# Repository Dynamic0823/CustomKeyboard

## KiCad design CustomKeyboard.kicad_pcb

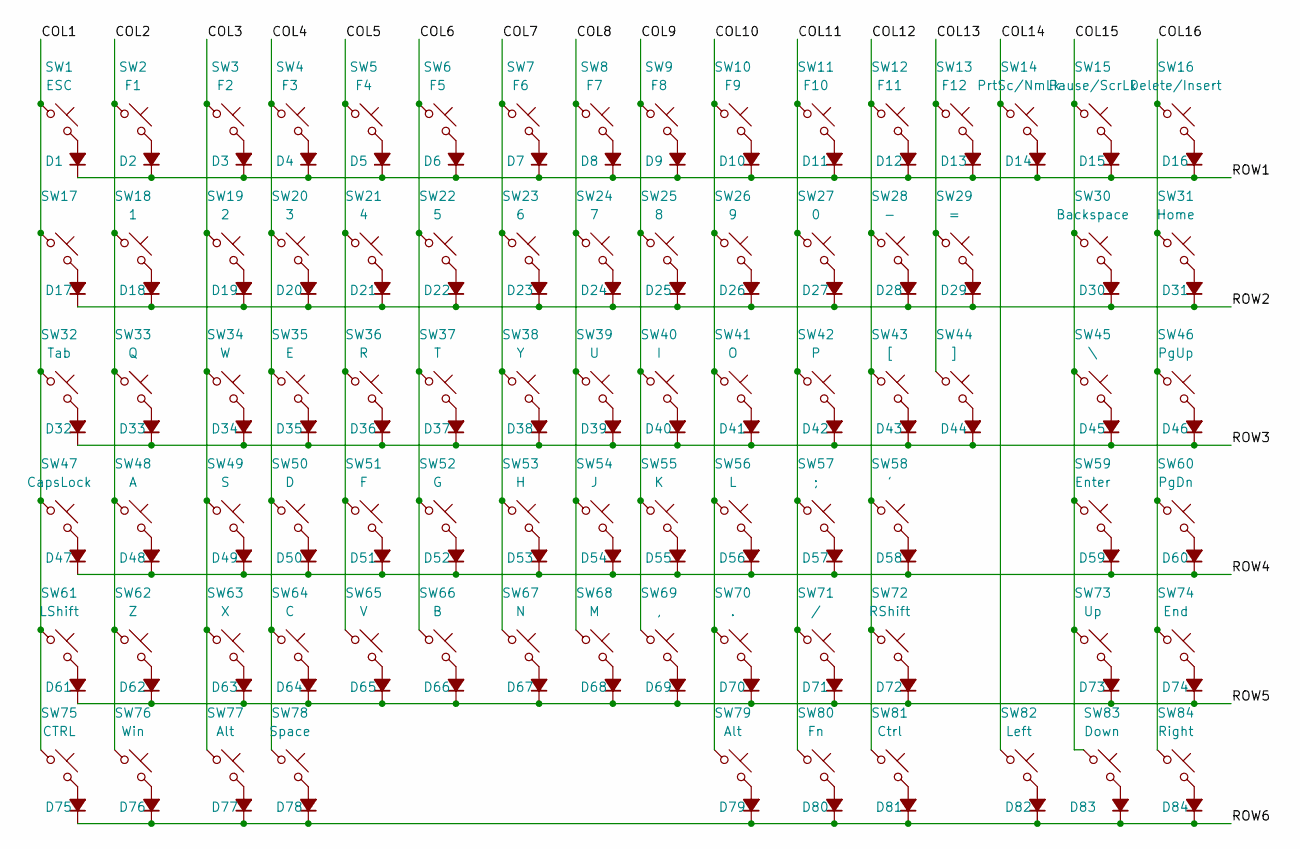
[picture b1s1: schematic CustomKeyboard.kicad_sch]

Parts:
D1, D2, D3, D4, D5, D6, D7, D8, D9, D10, D11, D12, D13, D14, D15, D16, D17, D18, D19, D20, D21, D22, D23, D24, D25, D26, D27, D28, D29, D30, D31, D32, D33, D34, D35, D36, D37, D38, D39, D40, D41, D42, D43, D44, D45, D46, D47, D48, D49, D50, D51, D52, D53, D54, D55, D56, D57, D58, D59, D60, D61, D62, D63, D64, D65, D66, D67, D68, D69, D70, D71, D72, D73, D74, D75, D76, D77, D78, D79, D80, D81, D82, D83, D84: D_Small_Filled; D_0805_2012Metric_Pad1.15x1.40mm_HandSolder
SW1: ESC; SW_Hotswap_Kailh_Choc_V1V2_Plated_1.00u
SW2: F1; SW_Hotswap_Kailh_Choc_V1V2_Plated_1.00u
SW3: F2; SW_Hotswap_Kailh_Choc_V1V2_Plated_1.00u
SW4: F3; SW_Hotswap_Kailh_Choc_V1V2_Plated_1.00u
SW5: F4; SW_Hotswap_Kailh_Choc_V1V2_Plated_1.00u
SW6: F5; SW_Hotswap_Kailh_Choc_V1V2_Plated_1.00u
SW7: F6; SW_Hotswap_Kailh_Choc_V1V2_Plated_1.00u
SW8: F7; SW_Hotswap_Kailh_Choc_V1V2_Plated_1.00u
SW9: F8; SW_Hotswap_Kailh_Choc_V1V2_Plated_1.00u
SW10: F9; SW_Hotswap_Kailh_Choc_V1V2_Plated_1.00u
SW11: F10; SW_Hotswap_Kailh_Choc_V1V2_Plated_1.00u
SW12: F11; SW_Hotswap_Kailh_Choc_V1V2_Plated_1.00u
SW13: F12; SW_Hotswap_Kailh_Choc_V1V2_Plated_1.00u
SW14: PrtSc/NmLk; SW_Hotswap_Kailh_Choc_V1V2_Plated_1.00u
SW15: Pause/ScrLk; SW_Hotswap_Kailh_Choc_V1V2_Plated_1.00u
SW16: Delete/Insert; SW_Hotswap_Kailh_Choc_V1V2_Plated_1.00u
SW17: SW_Hotswap_Kailh_Choc_V1V2_Plated_1.00u
SW18: 1; SW_Hotswap_Kailh_Choc_V1V2_Plated_1.00u
SW19: 2; SW_Hotswap_Kailh_Choc_V1V2_Plated_1.00u
SW20: 3; SW_Hotswap_Kailh_Choc_V1V2_Plated_1.00u
SW21: 4; SW_Hotswap_Kailh_Choc_V1V2_Plated_1.00u
SW22: 5; SW_Hotswap_Kailh_Choc_V1V2_Plated_1.00u
SW23: 6; SW_Hotswap_Kailh_Choc_V1V2_Plated_1.00u
SW24: 7; SW_Hotswap_Kailh_Choc_V1V2_Plated_1.00u
SW25: 8; SW_Hotswap_Kailh_Choc_V1V2_Plated_1.00u
SW26: 9; SW_Hotswap_Kailh_Choc_V1V2_Plated_1.00u
SW27: 0; SW_Hotswap_Kailh_Choc_V1V2_Plated_1.00u
SW28: -; SW_Hotswap_Kailh_Choc_V1V2_Plated_1.00u
SW29: =; SW_Hotswap_Kailh_Choc_V1V2_Plated_1.00u
SW30: Backspace; SW_Hotswap_Kailh_Choc_V1V2_Plated_2.00u
SW31: Home; SW_Hotswap_Kailh_Choc_V1V2_Plated_1.00u
SW32: Tab; SW_Hotswap_Kailh_Choc_V1V2_Plated_1.50u
SW33: Q; SW_Hotswap_Kailh_Choc_V1V2_Plated_1.00u
SW34: W; SW_Hotswap_Kailh_Choc_V1V2_Plated_1.00u
SW35: E; SW_Hotswap_Kailh_Choc_V1V2_Plated_1.00u
SW36: R; SW_Hotswap_Kailh_Choc_V1V2_Plated_1.00u
SW37: T; SW_Hotswap_Kailh_Choc_V1V2_Plated_1.00u
SW38: Y; SW_Hotswap_Kailh_Choc_V1V2_Plated_1.00u
SW39: U; SW_Hotswap_Kailh_Choc_V1V2_Plated_1.00u
SW40: I; SW_Hotswap_Kailh_Choc_V1V2_Plated_1.00u
SW41: O; SW_Hotswap_Kailh_Choc_V1V2_Plated_1.00u
SW42: P; SW_Hotswap_Kailh_Choc_V1V2_Plated_1.00u
SW43: [; SW_Hotswap_Kailh_Choc_V1V2_Plated_1.00u
SW44: ]; SW_Hotswap_Kailh_Choc_V1V2_Plated_1.00u
SW45: \; SW_Hotswap_Kailh_Choc_V1V2_Plated_1.50u
SW46: PgUp; SW_Hotswap_Kailh_Choc_V1V2_Plated_1.00u
SW47: CapsLock; SW_Hotswap_Kailh_Choc_V1V2_Plated_1.75u
SW48: A; SW_Hotswap_Kailh_Choc_V1V2_Plated_1.00u
SW49: S; SW_Hotswap_Kailh_Choc_V1V2_Plated_1.00u
SW50: D; SW_Hotswap_Kailh_Choc_V1V2_Plated_1.00u
SW51: F; SW_Hotswap_Kailh_Choc_V1V2_Plated_1.00u
SW52: G; SW_Hotswap_Kailh_Choc_V1V2_Plated_1.00u
SW53: H; SW_Hotswap_Kailh_Choc_V1V2_Plated_1.00u
SW54: J; SW_Hotswap_Kailh_Choc_V1V2_Plated_1.00u
SW55: K; SW_Hotswap_Kailh_Choc_V1V2_Plated_1.00u
SW56: L; SW_Hotswap_Kailh_Choc_V1V2_Plated_1.00u
SW57: ;; SW_Hotswap_Kailh_Choc_V1V2_Plated_1.00u
SW58: '; SW_Hotswap_Kailh_Choc_V1V2_Plated_1.00u
SW59: Enter; SW_Hotswap_Kailh_Choc_V1V2_Plated_2.25u
SW60: PgDn; SW_Hotswap_Kailh_Choc_V1V2_Plated_1.00u
SW61: LShift; SW_Hotswap_Kailh_Choc_V1V2_Plated_2.25u
SW62: Z; SW_Hotswap_Kailh_Choc_V1V2_Plated_1.00u
SW63: X; SW_Hotswap_Kailh_Choc_V1V2_Plated_1.00u
SW64: C; SW_Hotswap_Kailh_Choc_V1V2_Plated_1.00u
SW65: V; SW_Hotswap_Kailh_Choc_V1V2_Plated_1.00u
SW66: B; SW_Hotswap_Kailh_Choc_V1V2_Plated_1.00u
SW67: N; SW_Hotswap_Kailh_Choc_V1V2_Plated_1.00u
SW68: M; SW_Hotswap_Kailh_Choc_V1V2_Plated_1.00u
SW69: ,; SW_Hotswap_Kailh_Choc_V1V2_Plated_1.00u
SW70: .; SW_Hotswap_Kailh_Choc_V1V2_Plated_1.00u
SW71: /; SW_Hotswap_Kailh_Choc_V1V2_Plated_1.00u
SW72: RShift; SW_Hotswap_Kailh_Choc_V1V2_Plated_1.75u
SW73: Up; SW_Hotswap_Kailh_Choc_V1V2_Plated_1.00u
SW74: End; SW_Hotswap_Kailh_Choc_V1V2_Plated_1.00u
SW75: CTRL; SW_Hotswap_Kailh_Choc_V1V2_Plated_1.25u
SW76: Win; SW_Hotswap_Kailh_Choc_V1V2_Plated_1.25u
SW77: Alt; SW_Hotswap_Kailh_Choc_V1V2_Plated_1.25u
SW78: Space; SW_Hotswap_Kailh_Choc_V1V2_Plated_6.25u
SW79: Alt; SW_Hotswap_Kailh_Choc_V1V2_Plated_1.00u
SW80: Fn; SW_Hotswap_Kailh_Choc_V1V2_Plated_1.00u
SW81: Ctrl; SW_Hotswap_Kailh_Choc_V1V2_Plated_1.00u
SW82: Left; SW_Hotswap_Kailh_Choc_V1V2_Plated_1.00u
SW83: Down; SW_Hotswap_Kailh_Choc_V1V2_Plated_1.00u
SW84: Right; SW_Hotswap_Kailh_Choc_V1V2_Plated_1.00u

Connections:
/COL1: SW1.1, SW17.1, SW32.1, SW47.1, SW61.1, SW75.1; also elsewhere on the board
/COL2: SW2.1, SW18.1, SW33.1, SW48.1, SW62.1, SW76.1; also elsewhere on the board
/COL3: SW3.1, SW19.1, SW34.1, SW49.1, SW63.1, SW77.1; also elsewhere on the board
/COL4: SW4.1, SW20.1, SW35.1, SW50.1, SW64.1, SW78.1; also elsewhere on the board
/COL5: SW5.1, SW21.1, SW36.1, SW51.1, SW65.1; also elsewhere on the board
/COL6: SW6.1, SW22.1, SW37.1, SW52.1, SW66.1; also elsewhere on the board
/COL7: SW7.1, SW23.1, SW38.1, SW53.1, SW67.1; also elsewhere on the board
/COL8: SW8.1, SW24.1, SW39.1, SW54.1, SW68.1; also elsewhere on the board
/COL9: SW9.1, SW25.1, SW40.1, SW55.1, SW69.1; also elsewhere on the board
/COL10: SW10.1, SW26.1, SW41.1, SW56.1, SW70.1, SW79.1; also elsewhere on the board
/COL11: SW11.1, SW27.1, SW42.1, SW57.1, SW71.1, SW80.1; also elsewhere on the board
/COL12: SW12.1, SW28.1, SW43.1, SW58.1, SW72.1, SW81.1; also elsewhere on the board
/COL13: SW13.1, SW29.1, SW44.1; also elsewhere on the board
/COL14: SW14.1, SW82.1; also elsewhere on the board
/COL15: SW15.1, SW30.1, SW45.1, SW59.1, SW73.1, SW83.1; also elsewhere on the board
/COL16: SW16.1, SW31.1, SW46.1, SW60.1, SW74.1, SW84.1; also elsewhere on the board
/ROW1: D1.1 (K), D2.1 (K), D3.1 (K), D4.1 (K), D5.1 (K), D6.1 (K), D7.1 (K), D8.1 (K), D9.1 (K), D10.1 (K), D11.1 (K), D12.1 (K), D13.1 (K), D14.1 (K), D15.1 (K), D16.1 (K); also elsewhere on the board
/ROW2: D17.1 (K), D18.1 (K), D19.1 (K), D20.1 (K), D21.1 (K), D22.1 (K), D23.1 (K), D24.1 (K), D25.1 (K), D26.1 (K), D27.1 (K), D28.1 (K), D29.1 (K), D30.1 (K), D31.1 (K); also elsewhere on the board
/ROW3: D32.1 (K), D33.1 (K), D34.1 (K), D35.1 (K), D36.1 (K), D37.1 (K), D38.1 (K), D39.1 (K), D40.1 (K), D41.1 (K), D42.1 (K), D43.1 (K), D44.1 (K), D45.1 (K), D46.1 (K); also elsewhere on the board
/ROW4: D47.1 (K), D48.1 (K), D49.1 (K), D50.1 (K), D51.1 (K), D52.1 (K), D53.1 (K), D54.1 (K), D55.1 (K), D56.1 (K), D57.1 (K), D58.1 (K), D59.1 (K), D60.1 (K); also elsewhere on the board
/ROW5: D61.1 (K), D62.1 (K), D63.1 (K), D64.1 (K), D65.1 (K), D66.1 (K), D67.1 (K), D68.1 (K), D69.1 (K), D70.1 (K), D71.1 (K), D72.1 (K), D73.1 (K), D74.1 (K); also elsewhere on the board
/ROW6: D75.1 (K), D76.1 (K), D77.1 (K), D78.1 (K), D79.1 (K), D80.1 (K), D81.1 (K), D82.1 (K), D83.1 (K), D84.1 (K); also elsewhere on the board
unnamed: D1.2 (A), SW1.2
unnamed: D2.2 (A), SW2.2
unnamed: D3.2 (A), SW3.2
unnamed: D4.2 (A), SW4.2
unnamed: D5.2 (A), SW5.2
unnamed: D6.2 (A), SW6.2
unnamed: D7.2 (A), SW7.2
unnamed: D8.2 (A), SW8.2
unnamed: D9.2 (A), SW9.2
unnamed: D10.2 (A), SW10.2
unnamed: D11.2 (A), SW11.2
unnamed: D12.2 (A), SW12.2
unnamed: D13.2 (A), SW13.2
unnamed: D14.2 (A), SW14.2
unnamed: D15.2 (A), SW15.2
unnamed: D16.2 (A), SW16.2
unnamed: D17.2 (A), SW17.2
unnamed: D18.2 (A), SW18.2
unnamed: D19.2 (A), SW19.2
unnamed: D20.2 (A), SW20.2
unnamed: D21.2 (A), SW21.2
unnamed: D22.2 (A), SW22.2
unnamed: D23.2 (A), SW23.2
unnamed: D24.2 (A), SW24.2
unnamed: D25.2 (A), SW25.2
unnamed: D26.2 (A), SW26.2
unnamed: D27.2 (A), SW27.2
unnamed: D28.2 (A), SW28.2
unnamed: D29.2 (A), SW29.2
unnamed: D30.2 (A), SW30.2
unnamed: D31.2 (A), SW31.2
unnamed: D32.2 (A), SW32.2
unnamed: D33.2 (A), SW33.2
unnamed: D34.2 (A), SW34.2
unnamed: D35.2 (A), SW35.2
unnamed: D36.2 (A), SW36.2
unnamed: D37.2 (A), SW37.2
unnamed: D38.2 (A), SW38.2
unnamed: D39.2 (A), SW39.2
unnamed: D40.2 (A), SW40.2
unnamed: D41.2 (A), SW41.2
unnamed: D42.2 (A), SW42.2
unnamed: D43.2 (A), SW43.2
unnamed: D44.2 (A), SW44.2
unnamed: D45.2 (A), SW45.2
unnamed: D46.2 (A), SW46.2
unnamed: D47.2 (A), SW47.2
unnamed: D48.2 (A), SW48.2
unnamed: D49.2 (A), SW49.2
unnamed: D50.2 (A), SW50.2
unnamed: D51.2 (A), SW51.2
unnamed: D52.2 (A), SW52.2
unnamed: D53.2 (A), SW53.2
unnamed: D54.2 (A), SW54.2
unnamed: D55.2 (A), SW55.2
unnamed: D56.2 (A), SW56.2
unnamed: D57.2 (A), SW57.2
unnamed: D58.2 (A), SW58.2
unnamed: D59.2 (A), SW59.2
unnamed: D60.2 (A), SW60.2
unnamed: D61.2 (A), SW61.2
unnamed: D62.2 (A), SW62.2
unnamed: D63.2 (A), SW63.2
unnamed: D64.2 (A), SW64.2
unnamed: D65.2 (A), SW65.2
unnamed: D66.2 (A), SW66.2
unnamed: D67.2 (A), SW67.2
unnamed: D68.2 (A), SW68.2
unnamed: D69.2 (A), SW69.2
unnamed: D70.2 (A), SW70.2
unnamed: D71.2 (A), SW71.2
unnamed: D72.2 (A), SW72.2
unnamed: D73.2 (A), SW73.2
unnamed: D74.2 (A), SW74.2
unnamed: D75.2 (A), SW75.2
unnamed: D76.2 (A), SW76.2
unnamed: D77.2 (A), SW77.2
unnamed: D78.2 (A), SW78.2
unnamed: D79.2 (A), SW79.2
unnamed: D80.2 (A), SW80.2
unnamed: D81.2 (A), SW81.2
unnamed: D82.2 (A), SW82.2
unnamed: D83.2 (A), SW83.2
unnamed: D84.2 (A), SW84.2

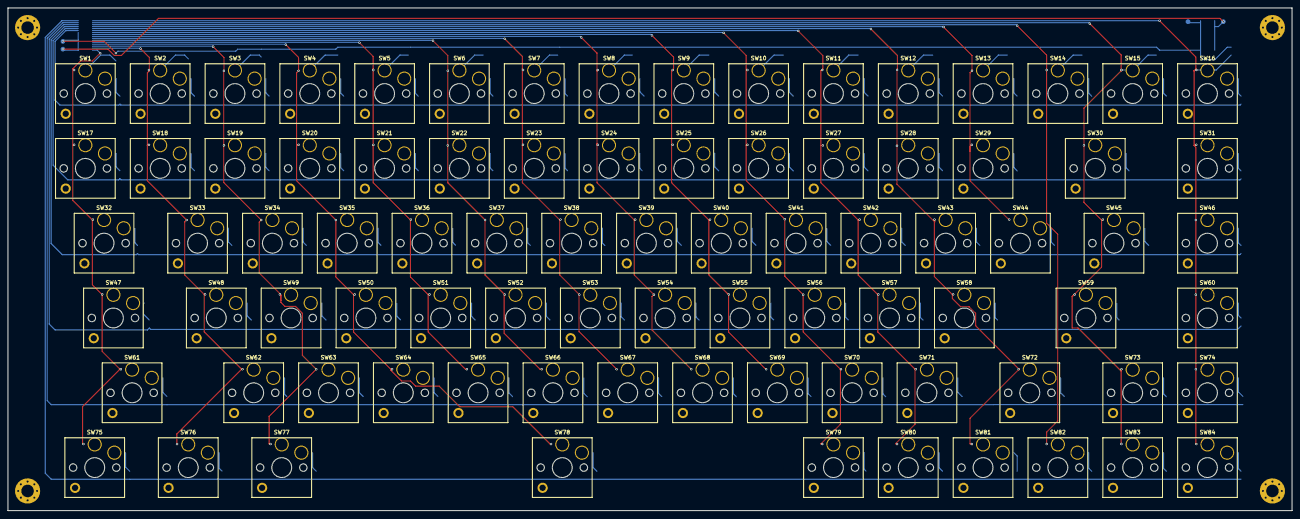
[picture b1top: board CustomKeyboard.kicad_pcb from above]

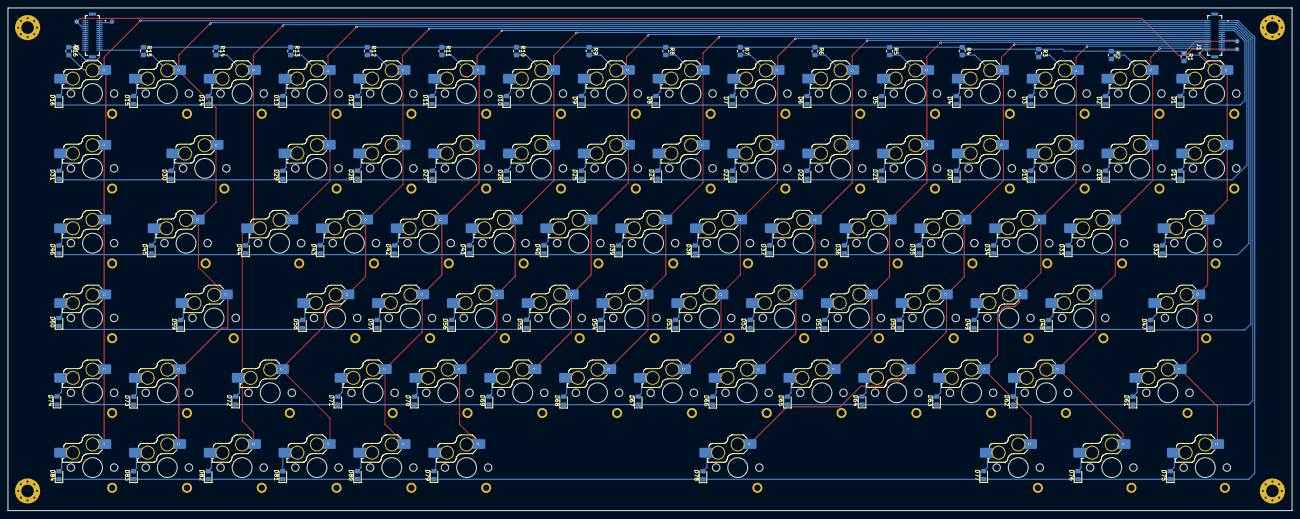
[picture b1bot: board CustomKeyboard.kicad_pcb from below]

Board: 2 copper layers, 327.0 x 128.0 mm, 190 parts (102 on the bottom side), 108 nets.

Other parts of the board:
H1, H2, H3, H4: MountingHole; MountingHole_3.2mm_M3_Pad_Via
J1, J2: Conn_02x16_Odd_Even; HRS_DF12NB_3.0_-32DS-0.5V_51_
R1, R2, R3, R4, R5, R6, R7, R8, R9, R10, R11, R12, R13, R14, R15, R16: 10k; R_0805_2012Metric_Pad1.20x1.40mm_HandSolder

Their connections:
+3.3V: J1.13, J1.15, J1.17, J1.19, J1.21, J2.1, J2.3, J2.5, J2.7, J2.9, J2.11, J2.13, J2.15, J2.17, J2.19, J2.21, J2.23, J2.25, J2.27, J2.29, J2.31, R1.1, R2.1, R3.1, R4.1, R5.1, R6.1, R7.1, R8.1, R9.1, R10.1, R11.1, R12.1, R13.1, R14.1, R15.1, R16.1
/COL1: J1.32, R1.2; also elsewhere on the board
/COL2: J1.30, R2.2; also elsewhere on the board
/COL3: J1.28, R3.2; also elsewhere on the board
/COL4: J1.26, R4.2; also elsewhere on the board
/COL5: J1.24, R5.2; also elsewhere on the board
/COL6: J1.22, R6.2; also elsewhere on the board
/COL7: J1.20, R7.2; also elsewhere on the board
/COL8: J1.18, R8.2; also elsewhere on the board
/COL9: J1.16, R9.2; also elsewhere on the board
/COL10: J1.14, R10.2; also elsewhere on the board
/COL11: J1.12, R11.2; also elsewhere on the board
/COL12: J1.10, R12.2; also elsewhere on the board
/COL13: J1.8, R13.2; also elsewhere on the board
/COL14: J1.6, R14.2; also elsewhere on the board
/COL15: J1.4, R15.2; also elsewhere on the board
/COL16: J1.2, R16.2; also elsewhere on the board
/ROW1: J1.11; also elsewhere on the board
/ROW2: J1.9; also elsewhere on the board
/ROW3: J1.7; also elsewhere on the board
/ROW4: J1.5; also elsewhere on the board
/ROW5: J1.3; also elsewhere on the board
/ROW6: J1.1; also elsewhere on the board
GND: J1.23, J1.25, J1.27, J1.29, J1.31, J2.2, J2.4, J2.6, J2.8, J2.10, J2.12, J2.14, J2.16, J2.18, J2.20, J2.22, J2.24, J2.26, J2.28, J2.30, J2.32

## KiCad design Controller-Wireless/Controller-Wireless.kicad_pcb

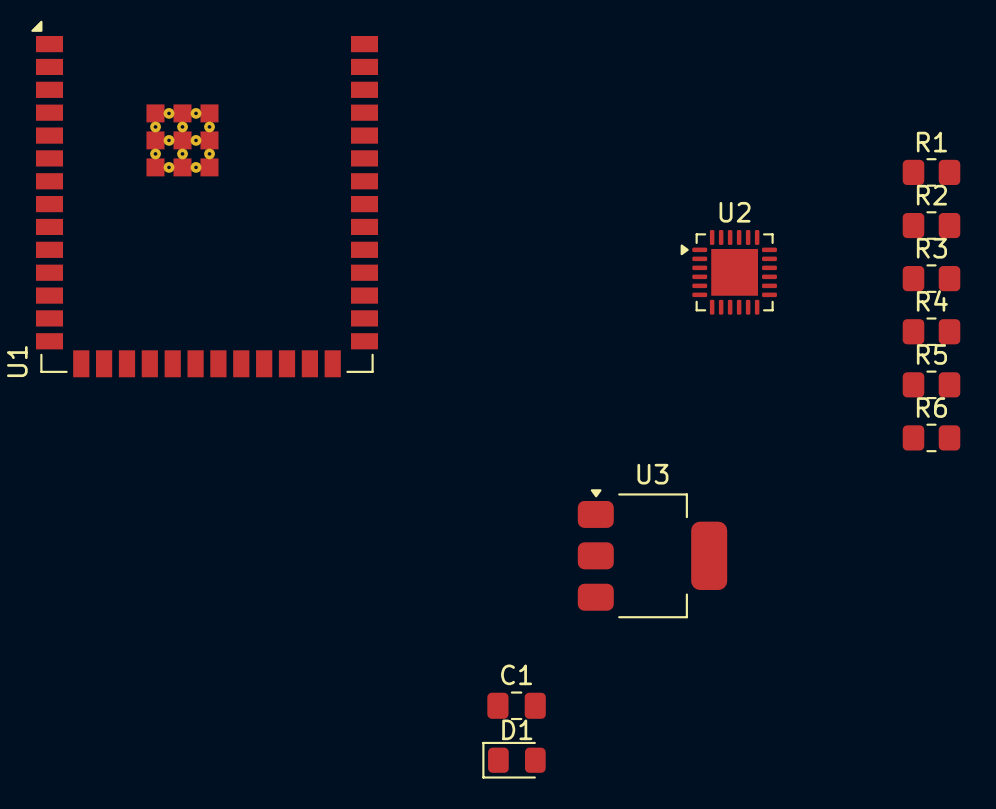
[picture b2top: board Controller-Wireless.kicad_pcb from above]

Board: 2 copper layers, 11 parts (0 on the bottom side), 9 nets, no tracks yet.

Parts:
C1: C_Small; C_0805_2012Metric_Pad1.18x1.45mm_HandSolder
D1: LED; D_0805_2012Metric_Pad1.15x1.40mm_HandSolder
R1, R2, R3, R6: 470; R_0805_2012Metric_Pad1.20x1.40mm_HandSolder
R4: 12K; R_0805_2012Metric_Pad1.20x1.40mm_HandSolder
R5: 12k; R_0805_2012Metric_Pad1.20x1.40mm_HandSolder
U1: ESP32-S3-WROOM-2
U2: CP2102N-Axx-xQFN24; QFN-24-1EP_4x4mm_P0.5mm_EP2.6x2.6mm
U3: AMS1117-3.3; SOT-223-3_TabPin2

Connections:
/EN: R2.2, R4.1, U1.3 (EN)
/IO0: R3.2, R5.1, U1.27 (IO0)
/U0Rx: R6.2, U1.36 (RXD0/IO44)
/U0Tx: U1.37 (TXD0/IO43), U2.21 (TXD)
GND: D1.1 (K), U1.1 (GND), U1.40 (GND), U1.41 (GND), U2.2 (GND), U2.25 (GND)
unnamed: D1.2 (A), R1.2
unnamed: R1.1, U1.38 (IO2)
unnamed: R6.1, U2.20 (RXD)
VDD: R4.2, R5.2, U1.2 (3V3)

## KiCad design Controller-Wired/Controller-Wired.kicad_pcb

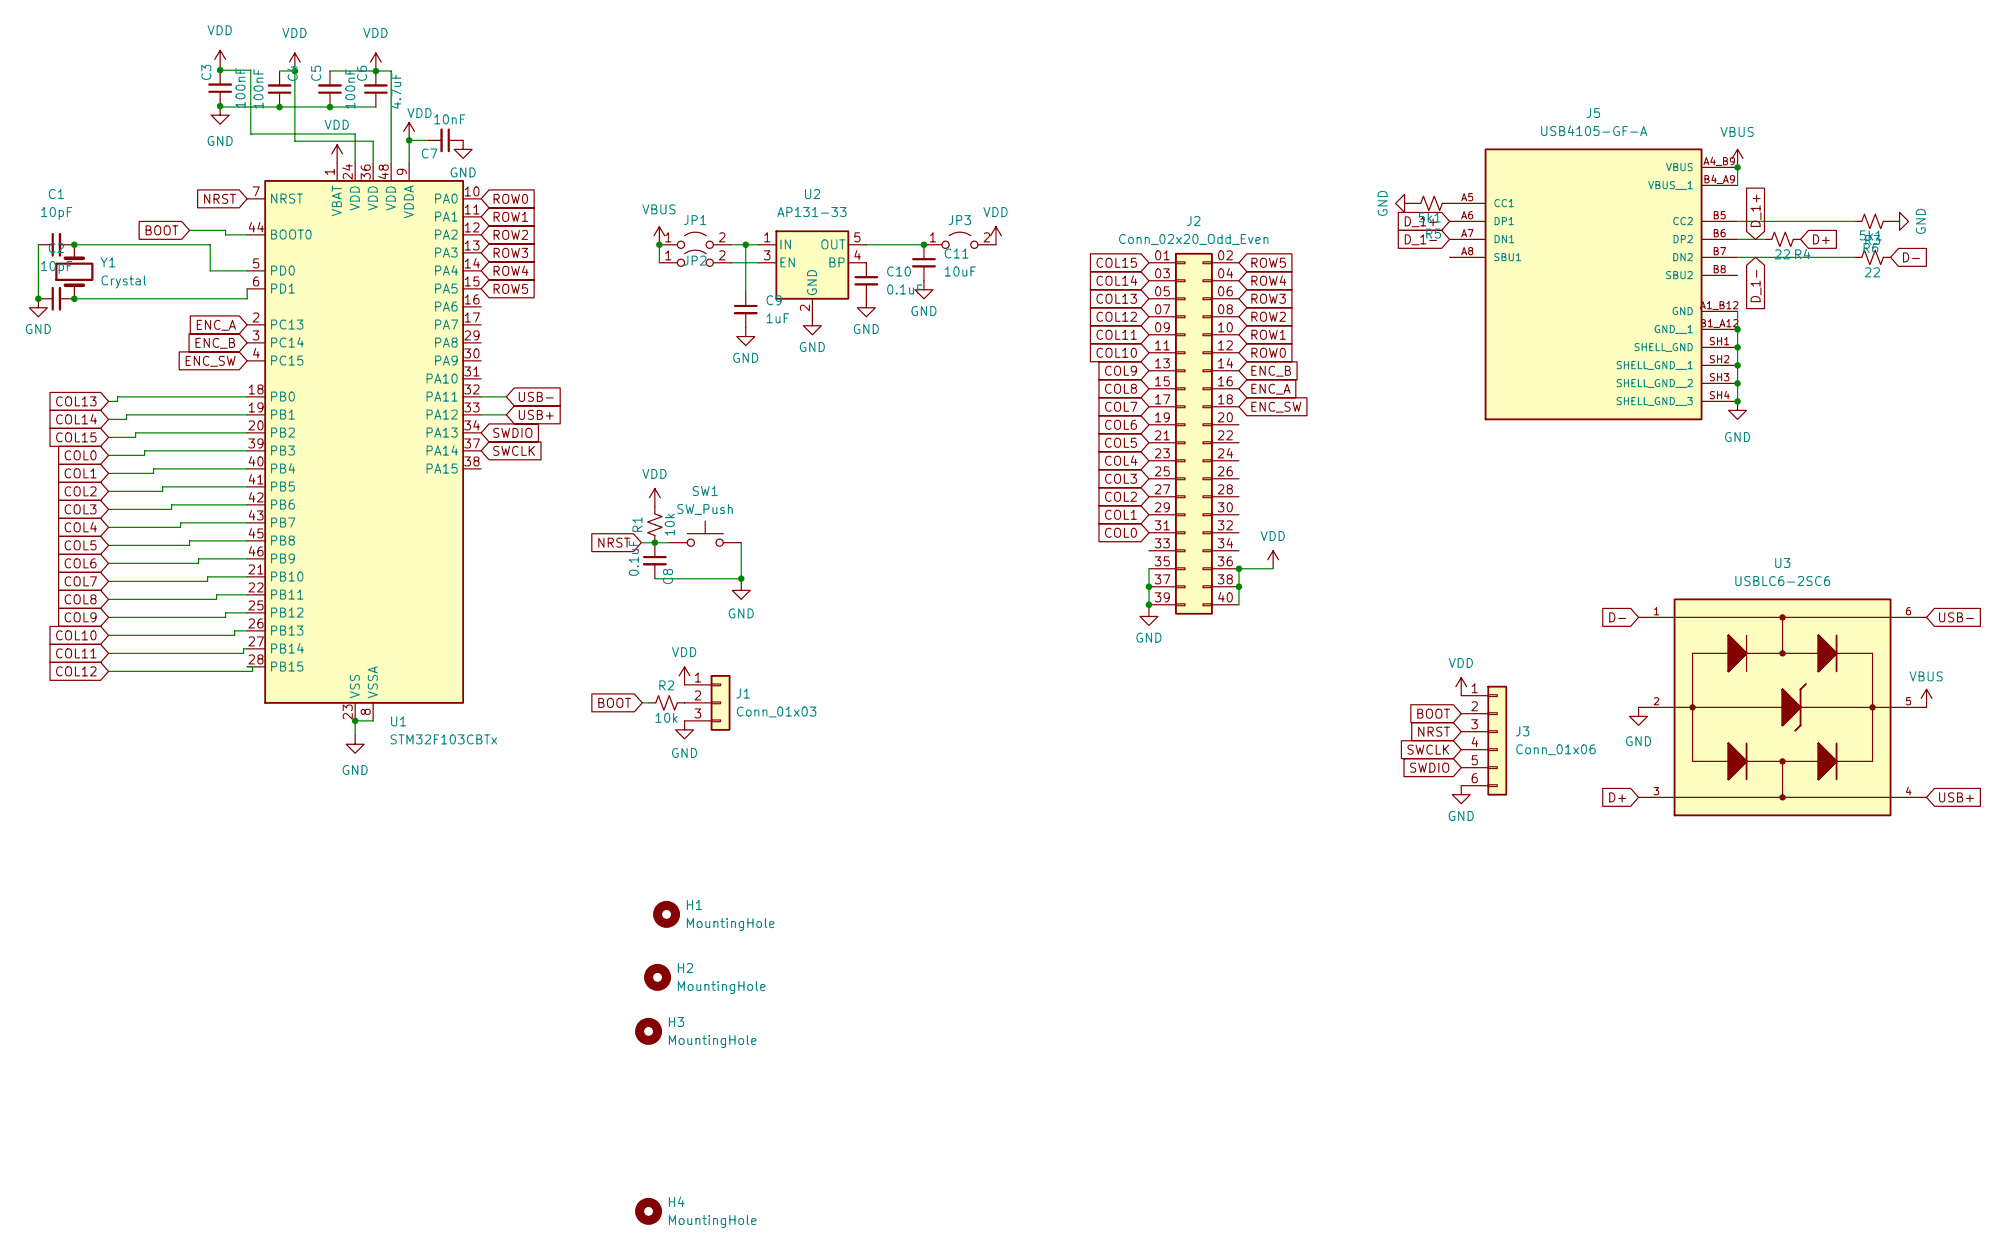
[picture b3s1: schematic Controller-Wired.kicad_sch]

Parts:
C1, C2: 10pF; C_0805_2012Metric_Pad1.18x1.45mm_HandSolder
C3, C4, C5: 100nF; C_0805_2012Metric_Pad1.18x1.45mm_HandSolder
C6: 4.7uF; C_0805_2012Metric_Pad1.18x1.45mm_HandSolder
C7: 10nF; C_0805_2012Metric_Pad1.18x1.45mm_HandSolder
C8, C10: 0.1uF; C_0805_2012Metric_Pad1.18x1.45mm_HandSolder
C9: 1uF; C_0805_2012Metric_Pad1.18x1.45mm_HandSolder
C11: 10uF; C_0805_2012Metric_Pad1.18x1.45mm_HandSolder
H1, H2, H3, H4: MountingHole; MountingHole_3.2mm_M3_Pad_Via
J1: Conn_01x03; PinHeader_1x03_P2.54mm_Vertical
J2: Conn_02x20_Odd_Even; SAMTEC_ERM8-020-X-X-DV; DigikeyPN SAM13720TR-ND
J3: Conn_01x06; PinHeader_1x06_P2.54mm_Vertical
J5: USB4105-GF-A; GCT_USB4105-GF-A; PARTREV B4
JP1, JP2, JP3: Jumper_2_Open; PinHeader_1x02_P2.54mm_Vertical
R1, R2: 10k; R_0805_2012Metric_Pad1.20x1.40mm_HandSolder
R3, R4: 22; R_0805_2012Metric_Pad1.20x1.40mm_HandSolder
R5, R6: 5k1; R_0805_2012Metric_Pad1.20x1.40mm_HandSolder
SW1: SW_Push; SW_SPST_B3SL-1002P; DigikeyPN SW1064TR-ND
U1: STM32F103CBTx; LQFP-48_7x7mm_P0.5mm; DigikeyPN 497-17380-2-ND
U2: AP131-33; SOT-23-5
U3: USBLC6-2SC6; SOT95P280X145-6N
Y1: Crystal; XTAL_ABM3-8.000MHZ-D2Y-T_ABR; DigikeyPN 535-10630-2-ND

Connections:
BOOT: J3.2, R2.1, U1.44 (BOOT0)
COL0: J2.31, U1.39 (PB3)
COL1: J2.29, U1.40 (PB4)
COL2: J2.27, U1.41 (PB5)
COL3: J2.25, U1.42 (PB6)
COL4: J2.23, U1.43 (PB7)
COL5: J2.21, U1.45 (PB8)
COL6: J2.19, U1.46 (PB9)
COL7: J2.17, U1.21 (PB10)
COL8: J2.15, U1.22 (PB11)
COL9: J2.13, U1.25 (PB12)
COL10: J2.11, U1.26 (PB13)
COL11: J2.09 (Pin_9), U1.27 (PB14)
COL12: J2.07 (Pin_7), U1.28 (PB15)
COL13: J2.05 (Pin_5), U1.18 (PB0)
COL14: J2.03 (Pin_3), U1.19 (PB1)
COL15: J2.01 (Pin_1), U1.20 (PB2)
D+: R4.2, U3.3
D-: R3.2, U3.1
D_1+: J5.A6 (DP1), J5.B6 (DP2), R4.1
D_1-: J5.A7 (DN1), J5.B7 (DN2), R3.1
ENC_A: J2.16, U1.2 (PC13)
ENC_B: J2.14, U1.3 (PC14)
ENC_SW: J2.18, U1.4 (PC15)
GND: C1.1, C2.1, C3.1, C4.1, C5.1, C6.1, C7.1, C8.2, C9.2, C10.2, C11.2, J1.3, J2.35, J2.37, J2.39, J3.6, J5.A1_B12 (GND), J5.B1_A12 (GND__1), J5.SH1 (SHELL_GND), J5.SH2 (SHELL_GND__1), J5.SH3 (SHELL_GND__2), J5.SH4 (SHELL_GND__3), R5.2, R6.1, SW1.2, U1.8 (VSSA), U1.23 (VSS), U1.35 (VSS), U1.47 (VSS), U2.2 (GND), U3.2
NRST: C8.1, J3.3, R1.1, SW1.1, U1.7 (NRST)
unnamed: J1.2, R2.2
unnamed: J5.A5 (CC1), R5.1
unnamed: J5.B5 (CC2), R6.2
unnamed: C9.1, JP1.2 (B), U2.1 (IN)
unnamed: JP2.2 (B), U2.3 (EN)
unnamed: C11.1, JP3.1 (A), U2.5 (OUT)
unnamed: C1.2, U1.5 (PD0), Y1.2
unnamed: C2.2, U1.6 (PD1), Y1.1
unnamed: C10.1, U2.4 (BP)
ROW0: J2.12, U1.10 (PA0)
ROW1: J2.10, U1.11 (PA1)
ROW2: J2.08 (Pin_8), U1.12 (PA2)
ROW3: J2.06 (Pin_6), U1.13 (PA3)
ROW4: J2.04 (Pin_4), U1.14 (PA4)
ROW5: J2.02 (Pin_2), U1.15 (PA5)
SWCLK: J3.4, U1.37 (PA14)
SWDIO: J3.5, U1.34 (PA13)
USB+: U1.33 (PA12), U3.4
USB-: U1.32 (PA11), U3.6
VBUS: J5.A4_B9 (VBUS), J5.B4_A9 (VBUS__1), JP1.1 (A), JP2.1 (A), U3.5
VDD: C3.2, C4.2, C5.2, C6.2, C7.2, J1.1, J2.36, J2.38, J2.40, J3.1, JP3.2 (B), R1.2, U1.1 (VBAT), U1.9 (VDDA), U1.24 (VDD), U1.36 (VDD), U1.48 (VDD)

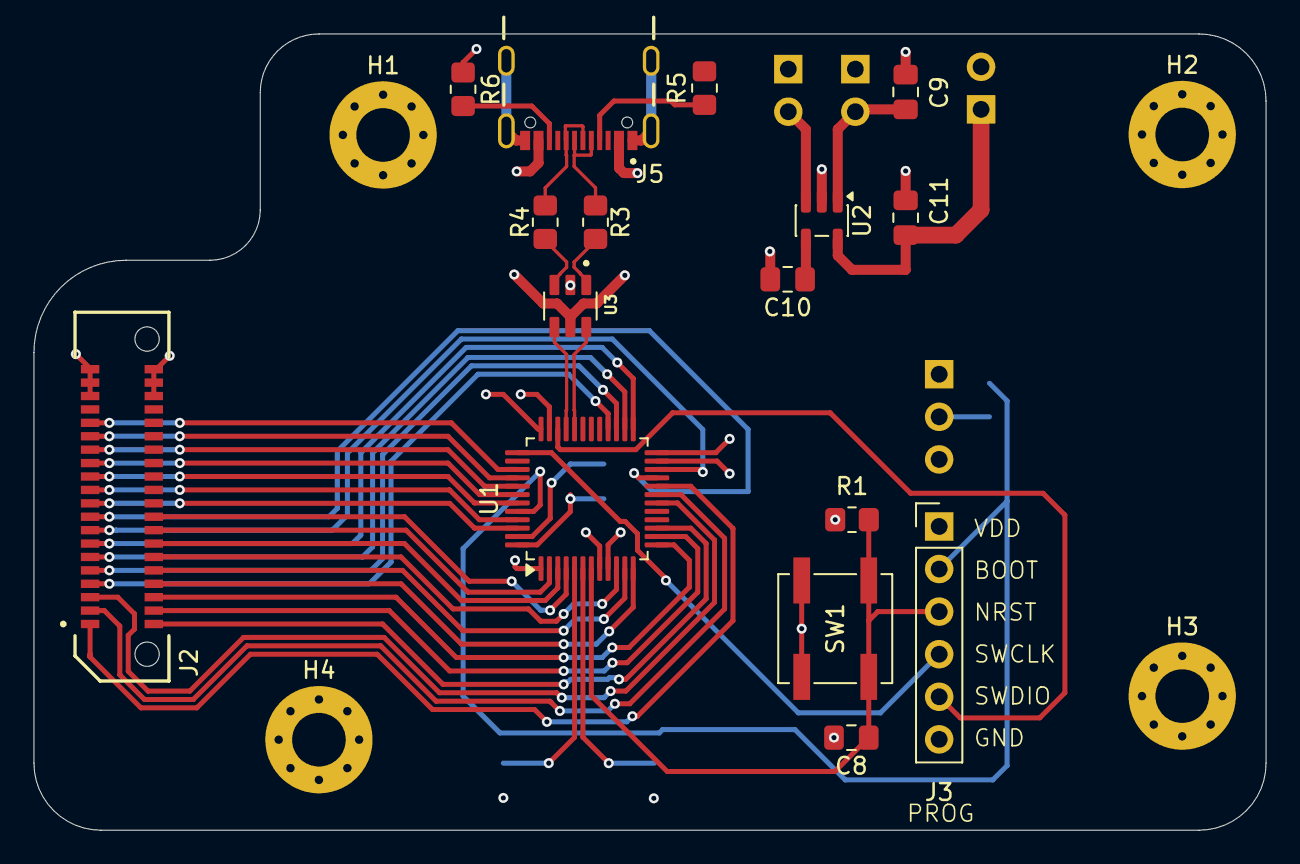
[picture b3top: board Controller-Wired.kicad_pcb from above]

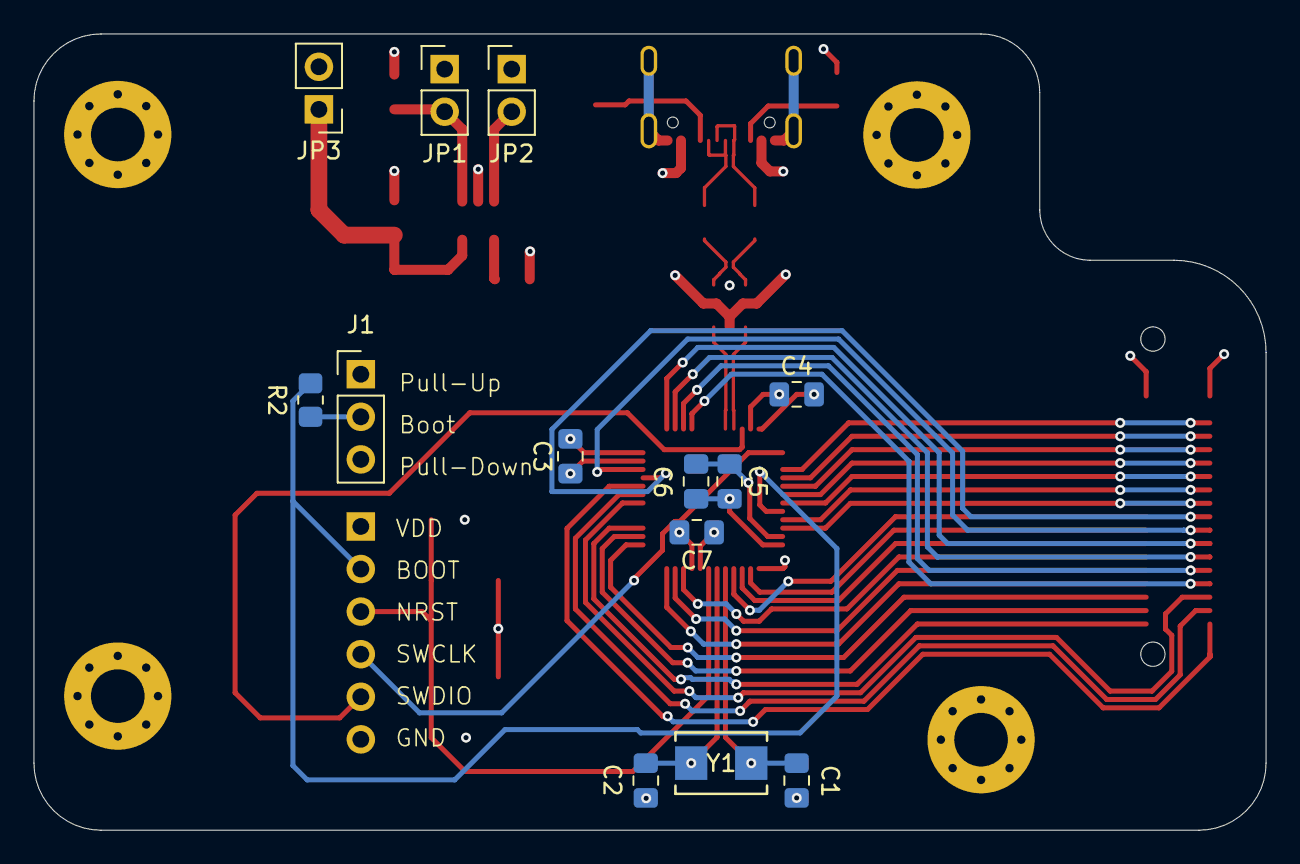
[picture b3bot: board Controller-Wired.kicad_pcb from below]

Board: 4 copper layers, 73.5 x 47.5 mm, 33 parts (13 on the bottom side), 47 nets.
